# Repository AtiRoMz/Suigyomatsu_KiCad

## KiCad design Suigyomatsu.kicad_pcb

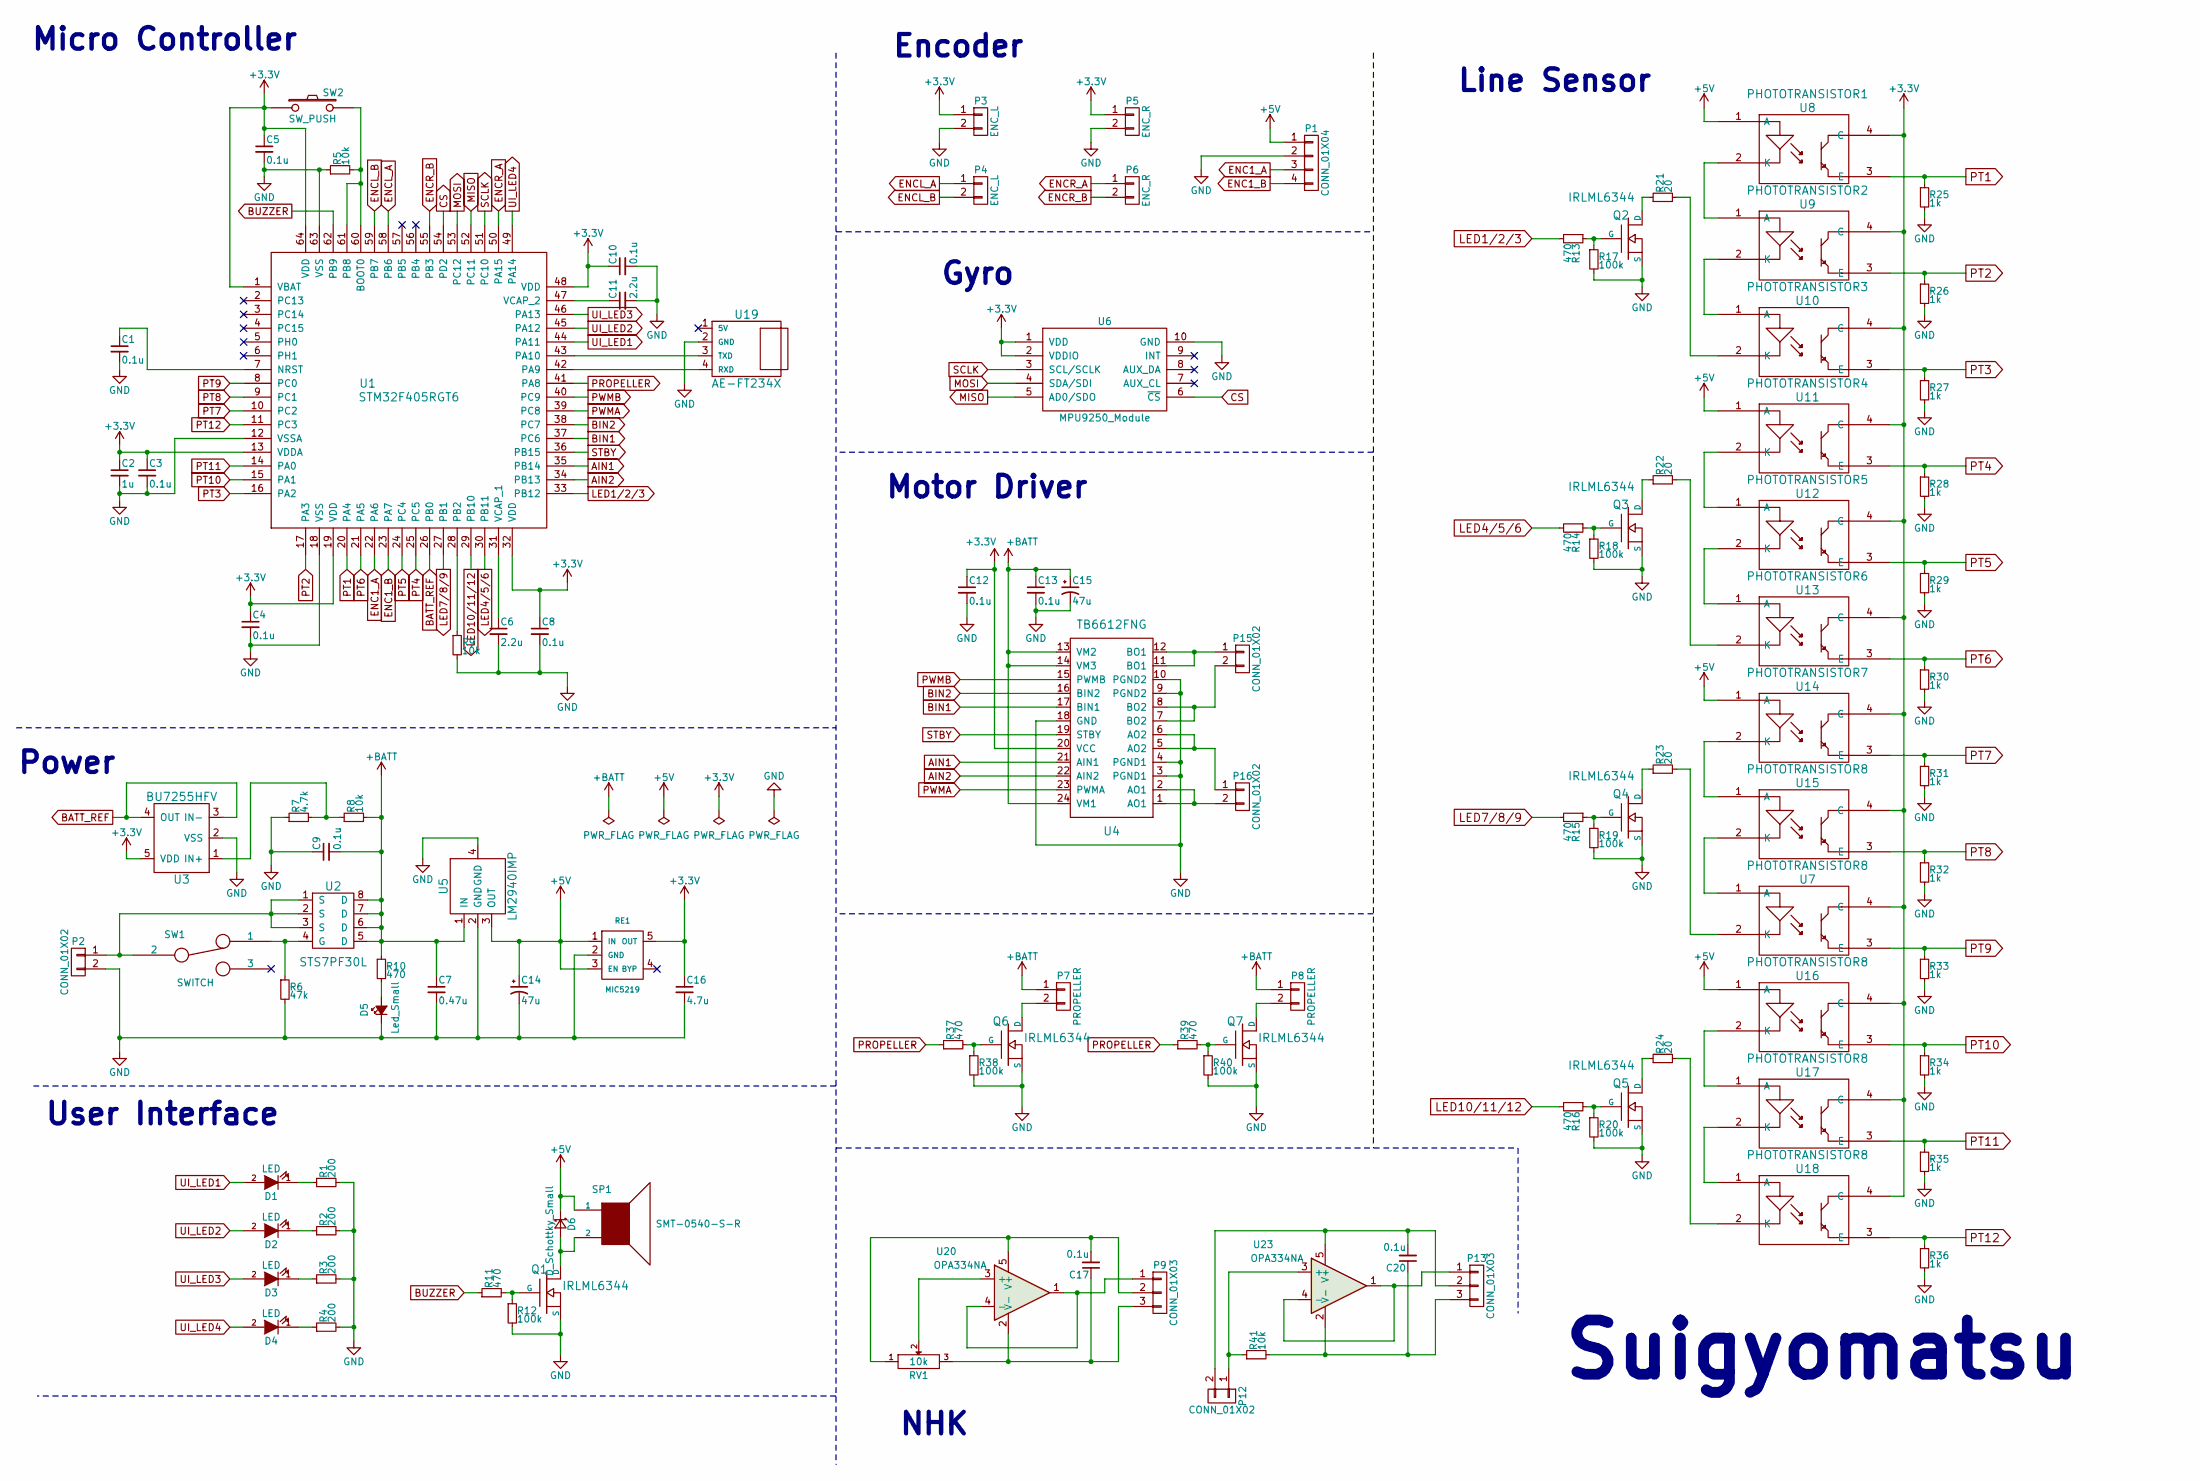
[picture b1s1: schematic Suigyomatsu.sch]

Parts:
C1, C3, C4, C5, C8, C9, C10, C12, C13, C17, C20: 0.1u; 1608
C2: 1u; 1608
C6, C11: 2.2u; 1608
C7: 0.47u; 1608
C14, C15: 47u; My_AlumiCapa_5mm
C16: 4.7u; 1608
D1, D2, D3, D4: LED; LED_1608
D5: Led_Small; LED_1608
D6: D_Schottky_Small; CUS520
P1: CONN_01X04; JST_PH_B4B-PH-K_04x2.00mm_Straight
P2, P12: CONN_01X02; JST_XH_B02B-XH-A_02x2.50mm_Straight
P3, P4: ENC_L; ENC_CON
P5, P6: ENC_R; ENC_CON
P7, P8: PROPELLER; ZH_2
P9, P13: CONN_01X03; JST_XH_B03B-XH-A_03x2.50mm_Straight
P15, P16: CONN_01X02; JST_PH_B2B-PH-K_02x2.00mm_Straight
Q1, Q2, Q3, Q4, Q5, Q6, Q7: IRLML6344; My_SOT-23
R1, R2, R3, R4: 200; 1608
R5, R8, R9, R41: 10k; 1608
R6: 47k; 1608
R7: 4.7k; 1608
R10, R11, R13, R14, R15, R16, R37, R39: 470; 1608
R12, R17, R18, R19, R20, R38, R40: 100k; 1608
R21, R22, R23, R24: 20; 1608
R25, R26, R27, R28, R29, R30, R31, R32, R33, R34, R35, R36: 1k; 1608
RE1: MIC5219; My_SOT-23-5
RV1: 10k; SV01A103AEA01
SP1: SMT-0540-S-R; SMT-0823-S-R
SW1: SWITCH; CL-SB-22A-01
SW2: SW_PUSH; PTS645SM43
U1: STM32F405RGT6; LQFP64
U2: STS7PF30L; SOIC-8_3.9x4.9mm_Pitch1.27mm
U3: BU7255HFV; My_HVSOF5
U4: TB6612FNG; SSOP-24_5.3x8.2mm_Pitch0.65mm
U5: LM2940IMP; My_SOT-223
U6: MPU9250_Module; MPU9250Module
U7, U15, U16, U17, U18: PHOTOTRANSISTOR8; LBR127HLD
U8: PHOTOTRANSISTOR1; LBR127HLD
U9: PHOTOTRANSISTOR2; LBR127HLD
U10: PHOTOTRANSISTOR3; LBR127HLD
U11: PHOTOTRANSISTOR4; LBR127HLD
U12: PHOTOTRANSISTOR5; LBR127HLD
U13: PHOTOTRANSISTOR6; LBR127HLD
U14: PHOTOTRANSISTOR7; LBR127HLD
U19: AE-FT234X
U20, U23: OPA334NA; My_SOT-23-5

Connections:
+3V3: C2.1, C3.1, C4.1, C5.1, C8.1, C10.1, C12.1, C16.1, P3.1, P5.1, RE1.5 (OUT), SW2.1, U1.1 (VBAT), U1.13 (VDDA), U1.19 (VDD), U1.32 (VDD), U1.48 (VDD), U1.64 (VDD), U3.5 (VDD), U4.20 (VCC), U6.1 (VDD), U6.2 (VDDIO), U7.4 (C), U8.4 (C), U9.4 (C), U10.4 (C), U11.4 (C), U12.4 (C), U13.4 (C), U14.4 (C), U15.4 (C), U16.4 (C), U17.4 (C), U18.4 (C)
+5V: C14.1, D6.1 (K), P1.1, RE1.1 (IN), RE1.3 (EN), SP1.1, U5.3 (OUT), U8.1 (A), U11.1 (A), U14.1 (A), U16.1 (A)
+BATT: C7.1, C9.2, C13.1, C15.1, P7.1, P8.1, R8.2, R10.1, U2.5 (D), U2.6 (D), U2.7 (D), U2.8 (D), U4.13 (VM2), U4.14 (VM3), U4.24 (VM1), U5.1 (IN)
AIN1: U1.35 (PB14), U4.21 (AIN1)
AIN2: U1.34 (PB13), U4.22 (AIN2)
BATT_REF: U1.26 (PB0), U3.3 (IN-), U3.4 (OUT)
BIN1: U1.37 (PC6), U4.17 (BIN1)
BIN2: U1.38 (PC7), U4.16 (BIN2)
BUZZER: R11.1, U1.62 (PB9)
CS: U1.54 (PD2), U6.6 (~CS)
ENC1_A: P1.3, U1.22 (PA6)
ENC1_B: P1.4, U1.23 (PA7)
ENCL_A: P4.1, U1.58 (PB6)
ENCL_B: P4.2, U1.59 (PB7)
ENCR_A: P6.1, U1.50 (PA15)
ENCR_B: P6.2, U1.55 (PB3)
GND: C1.2, C2.2, C3.2, C4.2, C5.2, C6.2, C7.2, C8.2, C9.1, C10.2, C11.2, C12.2, C13.2, C14.2, C15.2, C16.2, D5.1 (K), P1.2, P2.2, P3.2, P5.2, Q1.2 (S), Q2.2 (S), Q3.2 (S), Q4.2 (S), Q5.2 (S), Q6.2 (S), Q7.2 (S), R1.2, R2.2, R3.2, R4.2, R5.1, R6.2, R7.1, R9.2, R12.2, R17.2, R18.2, R19.2, R20.2, R25.2, R26.2, R27.2, R28.2, R29.2, R30.2, R31.2, R32.2, R33.2, R34.2, R35.2, R36.2, R38.2, R40.2, RE1.2 (GND), U1.12 (VSSA), U1.18 (VSS), U1.63 (VSS), U3.2 (VSS), U4.3 (PGND1), U4.4 (PGND1), U4.9 (PGND2), U4.10 (PGND2), U4.18 (GND), U5.2 (GND), U5.4 (GND), U6.10 (GND), U19.2 (GND)
LED1/2/3: R13.2, U1.33 (PB12)
LED4/5/6: R14.2, U1.30 (PB11)
LED7/8/9: R15.2, U1.27 (PB1)
LED10/11/12: R16.2, U1.29 (PB10)
MISO: U1.52 (PC11), U6.5 (AD0/SDO)
MOSI: U1.53 (PC12), U6.4 (SDA/SDI)
unnamed: C1.1, U1.7 (NRST)
unnamed: C6.1, U1.31 (VCAP_1)
unnamed: C11.1, U1.47 (VCAP_2)
unnamed 26: C17.1, P9.3, RV1.3, U20.2 (V-); also elsewhere on the board
unnamed 27: C17.2, P9.2, RV1.1, U20.5 (V+); also elsewhere on the board
unnamed: C20.1, P13.3, R41.2, U23.2 (V-)
unnamed: C20.2, P12.2, P13.2, U23.5 (V+)
unnamed: D1.1 (K), R1.1
unnamed: D2.1 (K), R2.1
unnamed: D3.1 (K), R3.1
unnamed: D4.1 (K), R4.1
unnamed: D5.2 (A), R10.2
unnamed: D6.2 (A), Q1.3 (D), SP1.2
unnamed: P2.1, SW1.2, U2.1 (S), U2.2 (S), U2.3 (S)
unnamed: P7.2, Q6.3 (D)
unnamed: P8.2, Q7.3 (D)
unnamed 39: P9.1, U20.1, U20.4 (-); also elsewhere on the board
unnamed: P12.1, R41.1, U23.3 (+)
unnamed: P13.1, U23.1, U23.4 (-)
unnamed: P15.1, U4.11 (BO1), U4.12 (BO1)
unnamed: P15.2, U4.7 (BO2), U4.8 (BO2)
unnamed: P16.1, U4.5 (AO2), U4.6 (AO2)
unnamed: P16.2, U4.1 (AO1), U4.2 (AO1)
unnamed: Q1.1 (G), R11.2, R12.1
unnamed: Q2.1 (G), R13.1, R17.1
unnamed: Q2.3 (D), R21.1
unnamed: Q3.1 (G), R14.1, R18.1
unnamed: Q3.3 (D), R22.1
unnamed: Q4.1 (G), R15.1, R19.1
unnamed: Q4.3 (D), R23.1
unnamed: Q5.1 (G), R16.1, R20.1
unnamed: Q5.3 (D), R24.1
unnamed: Q6.1 (G), R37.2, R38.1
unnamed: Q7.1 (G), R39.2, R40.1
unnamed: R5.2, SW2.2, U1.60 (BOOT0), U1.61 (PB8)
unnamed: R6.1, SW1.1, U2.4 (G)
unnamed: R7.2, R8.1, U3.1 (IN+)
unnamed: R9.1, U1.28 (PB2)
unnamed: R21.2, U10.2 (K)
unnamed: R22.2, U13.2 (K)
unnamed: R23.2, U7.2 (K)
unnamed: R24.2, U18.2 (K)
unnamed 65: RV1.2, U20.3 (+); also elsewhere on the board
unnamed: U1.42 (PA9), U19.4 (RXD)
unnamed: U1.43 (PA10), U19.3 (TXD)
unnamed: U8.2 (K), U9.1 (A)
unnamed: U9.2 (K), U10.1 (A)
unnamed: U11.2 (K), U12.1 (A)
unnamed: U12.2 (K), U13.1 (A)
unnamed: U14.2 (K), U15.1 (A)
unnamed: U7.1 (A), U15.2 (K)
unnamed: U16.2 (K), U17.1 (A)
unnamed: U17.2 (K), U18.1 (A)
PROPELLER: R37.1, R39.1, U1.41 (PA8)
PT1: R25.1, U1.20 (PA4), U8.3 (E)
PT2: R26.1, U1.17 (PA3), U9.3 (E)
PT3: R27.1, U1.16 (PA2), U10.3 (E)
PT4: R28.1, U1.25 (PC5), U11.3 (E)
PT5: R29.1, U1.24 (PC4), U12.3 (E)
PT6: R30.1, U1.21 (PA5), U13.3 (E)
PT7: R31.1, U1.10 (PC2), U14.3 (E)
PT8: R32.1, U1.9 (PC1), U15.3 (E)
PT9: R33.1, U1.8 (PC0), U7.3 (E)
PT10: R34.1, U1.15 (PA1), U16.3 (E)
PT11: R35.1, U1.14 (PA0), U17.3 (E)
PT12: R36.1, U1.11 (PC3), U18.3 (E)
PWMA: U1.39 (PC8), U4.23 (PWMA)
PWMB: U1.40 (PC9), U4.15 (PWMB)
SCLK: U1.51 (PC10), U6.3 (SCL/SCLK)
STBY: U1.36 (PB15), U4.19 (STBY)
UI_LED1: D1.2 (A), U1.44 (PA11)
UI_LED2: D2.2 (A), U1.45 (PA12)
UI_LED3: D3.2 (A), U1.46 (PA13)
UI_LED4: D4.2 (A), U1.49 (PA14)

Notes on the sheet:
Encoder
Micro Controller
Power
User Interface
Gyro
Motor Driver
Line Sensor
Suigyomatsu
NHK

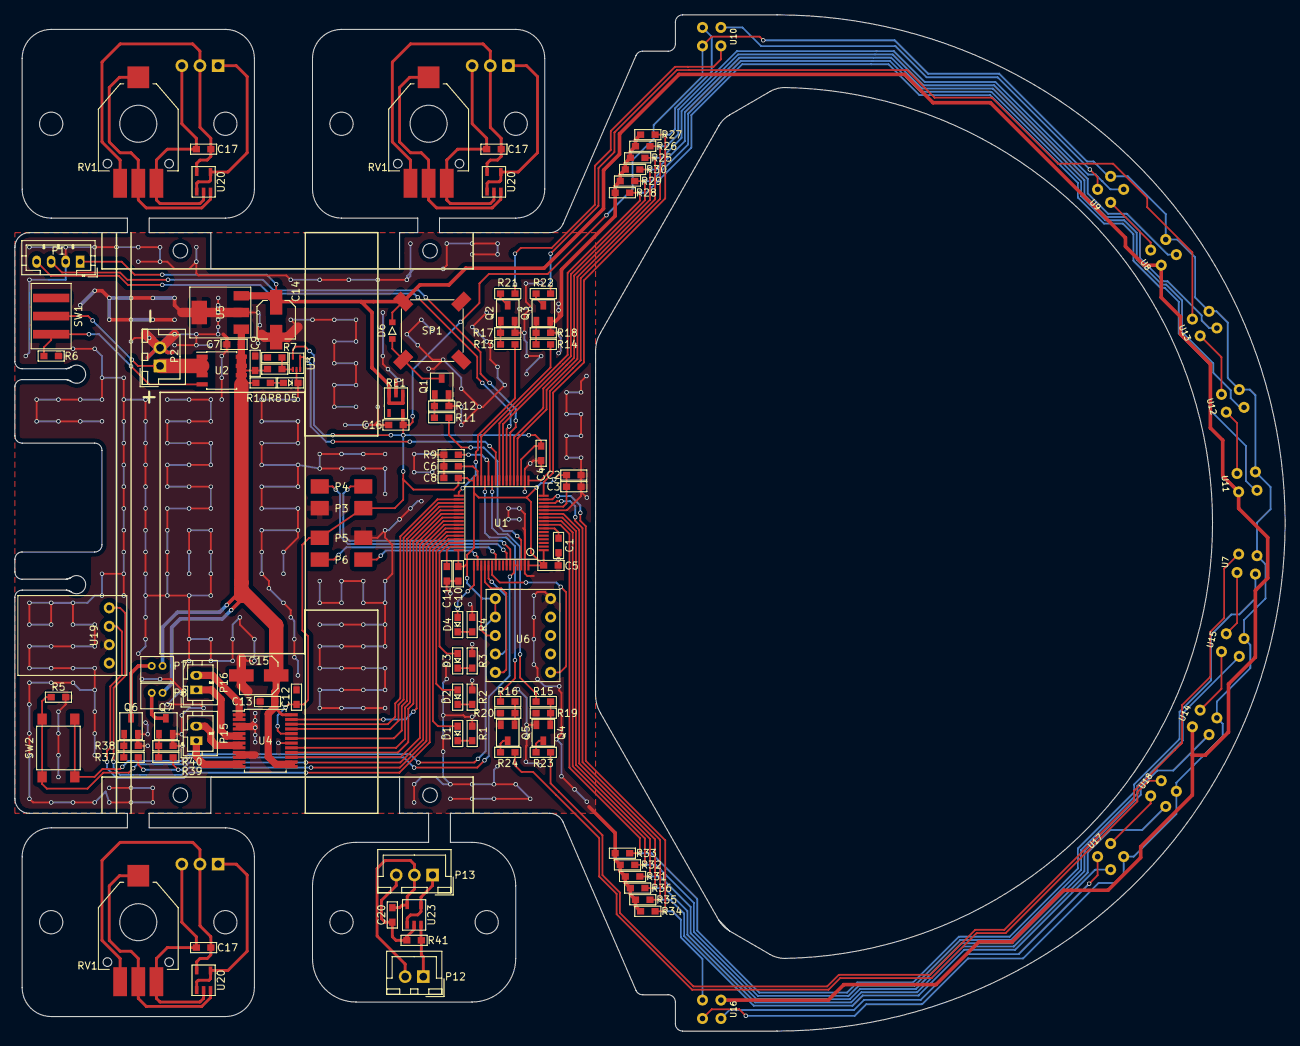
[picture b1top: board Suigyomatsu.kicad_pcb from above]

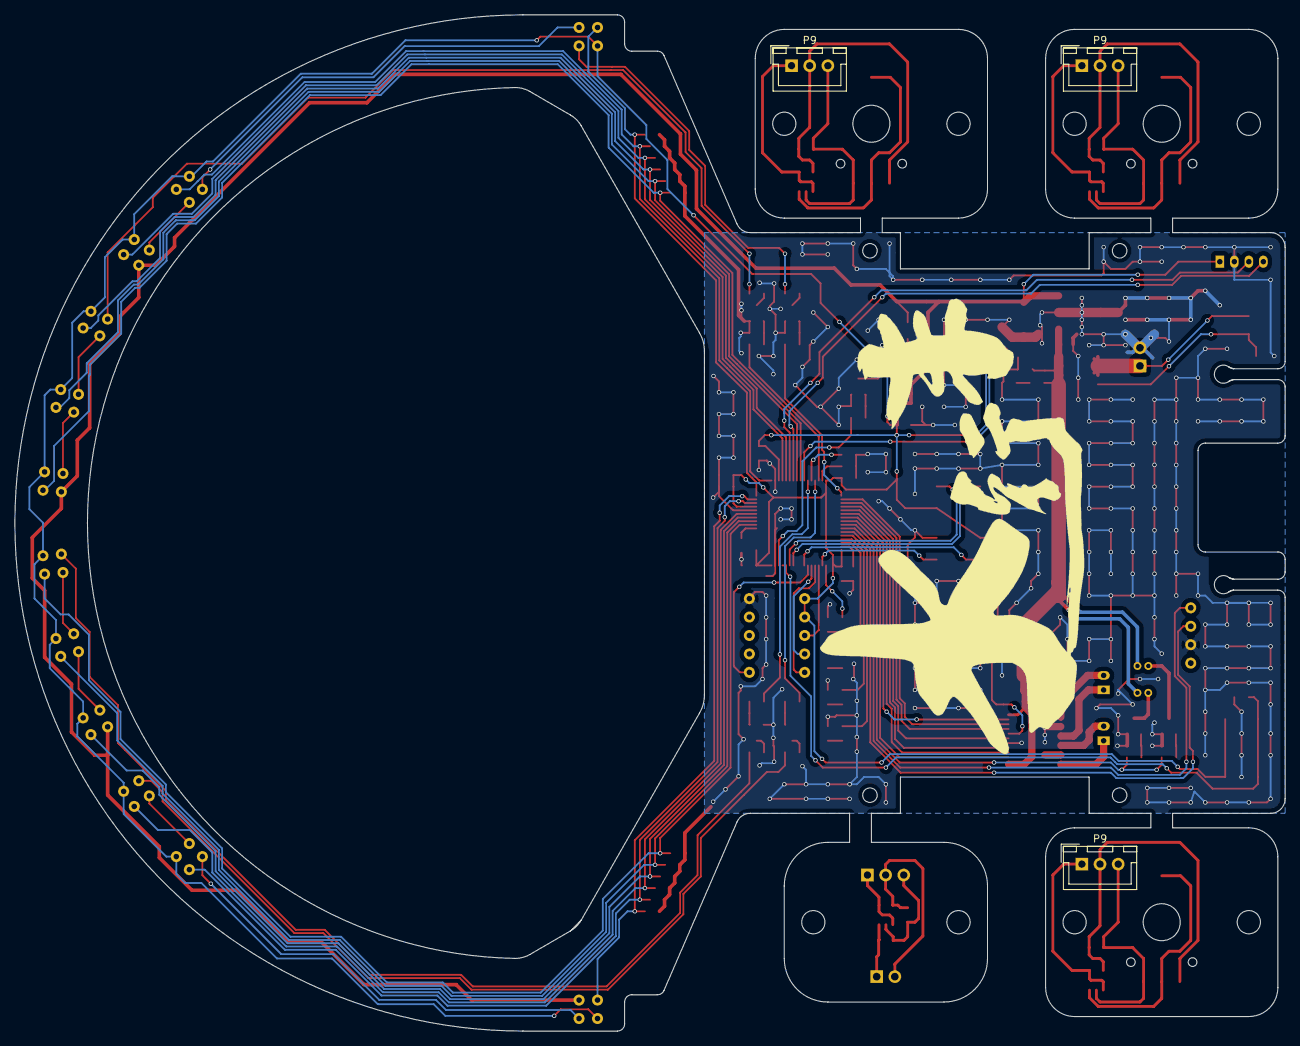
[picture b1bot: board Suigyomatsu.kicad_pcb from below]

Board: 2 copper layers, 175.0 x 140.0 mm, 119 parts (3 on the bottom side), 97 nets.

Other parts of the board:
C17#2, C17#3: 0.1u; 1608
P9#2, P9#3: CONN_01X03; JST_XH_B03B-XH-A_03x2.50mm_Straight
RV1#2, RV1#3: 10k; SV01A103AEA01
U20#2, U20#3: OPA334NA; My_SOT-23-5

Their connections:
unnamed 26: C17#2.1, C17#3.1, P9#2.3, P9#3.3, RV1#2.3, RV1#3.3, U20#2.2, U20#3.2; also elsewhere on the board
unnamed 27: C17#2.2, C17#3.2, P9#2.2, P9#3.2, RV1#2.1, RV1#3.1, U20#2.5, U20#3.5; also elsewhere on the board
unnamed 39: P9#2.1, P9#3.1, U20#2.1, U20#2.4, U20#3.1, U20#3.4; also elsewhere on the board
unnamed 65: RV1#2.2, RV1#3.2, U20#2.3, U20#3.3; also elsewhere on the board

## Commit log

2019-09-02 最初にして最後のコミット
